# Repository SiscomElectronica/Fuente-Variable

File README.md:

# Fuente-Variable

Fuente variable regulada con voltimetro 1.5 a 30V @ 1A

## Descripcion

El proyecto consta de 3 archivos importantes:

*Fuente_ESIQUIE_2.sch: Diagrama electrico del proyecto

*Fuente_ESIQUIE_2.brd: Archivo del diseño del circuito impreso

*Manual.pdf: Manual de Usuario & Garantia del Producto

## Consideraciones

Muchos componentes fueron modificados desde su libreria, asi que puede 
marcar algunos errores con respecto a su descarga y posterior modifcacion.

Con respecto a su fabricacion al no tener archivos (.gbr) gerber es 
necesario contactar al fabricante y proporcionarle el archivo 
Fuente_ESIQUIE_2.brd para su posterior manufacturacion.

Diseñado por: [Josue Echeverria](https://www.facebook.com/josue.echeverria.583)

Team SISCOM.

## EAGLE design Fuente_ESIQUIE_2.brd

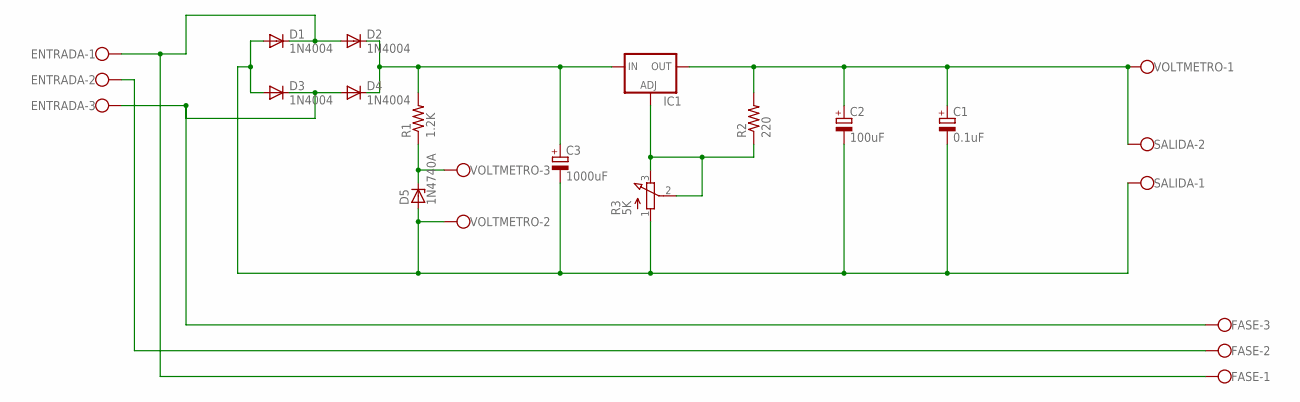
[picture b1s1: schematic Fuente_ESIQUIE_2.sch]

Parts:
C1: 0.1uF; E3,5-8
C2: 100uF; E3,5-8
C3: 1000uF; E7,5-16
D1, D2, D3, D4: 1N4004; DO41-10
D5: 1N4740A; DO41Z10
ENTRADA: W237-103
FASE: W237-103
IC1: LM317TS; 317TS
R1: 1.2K; 0207/12
R2: 220; 0207/12
R3: 5K; 3RP/1610N
SALIDA: W237-102
VOLTMETRO: W237-103

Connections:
unnamed: D1.C, D2.A, ENTRADA.1, FASE.1
unnamed: D3.C, D4.A, ENTRADA.3, FASE.3
unnamed: C1.-, C2.-, C3.-, D1.A, D3.A, D5.A, R3.1 (A), SALIDA.1, VOLTMETRO.2
unnamed: C3.+, D2.C, D4.C, IC1.3 (IN), R1.2
unnamed: IC1.1 (ADJ), R2.1, R3.2 (S), R3.3 (E)
unnamed: C1.+, C2.+, IC1.2 (OUT), R2.2, SALIDA.2, VOLTMETRO.1
unnamed: D5.C, R1.1, VOLTMETRO.3
unnamed: ENTRADA.2, FASE.2

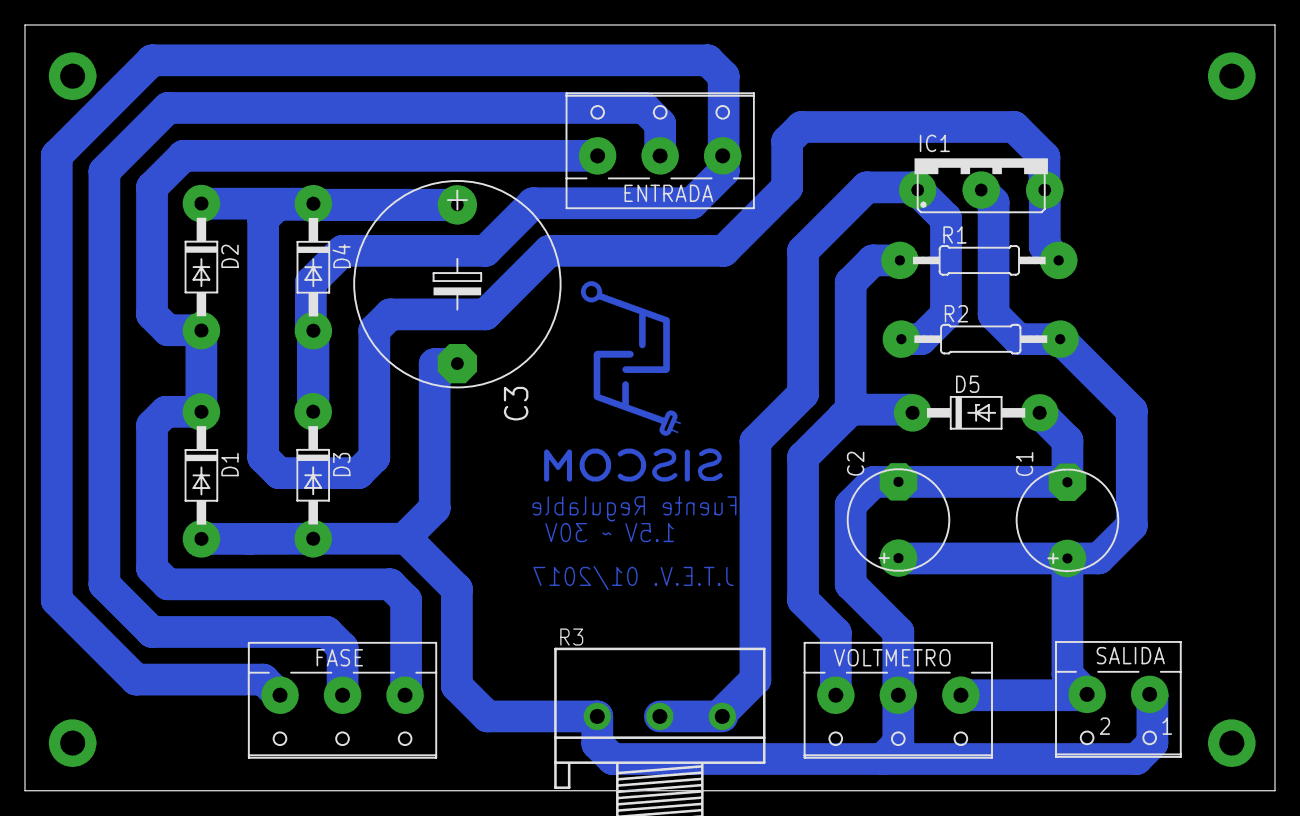
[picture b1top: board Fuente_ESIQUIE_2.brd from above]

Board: 2 copper layers, 100.0 x 61.2 mm, 16 parts (0 on the bottom side), 8 nets.

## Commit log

2017-08-16 Fuente V1.0
